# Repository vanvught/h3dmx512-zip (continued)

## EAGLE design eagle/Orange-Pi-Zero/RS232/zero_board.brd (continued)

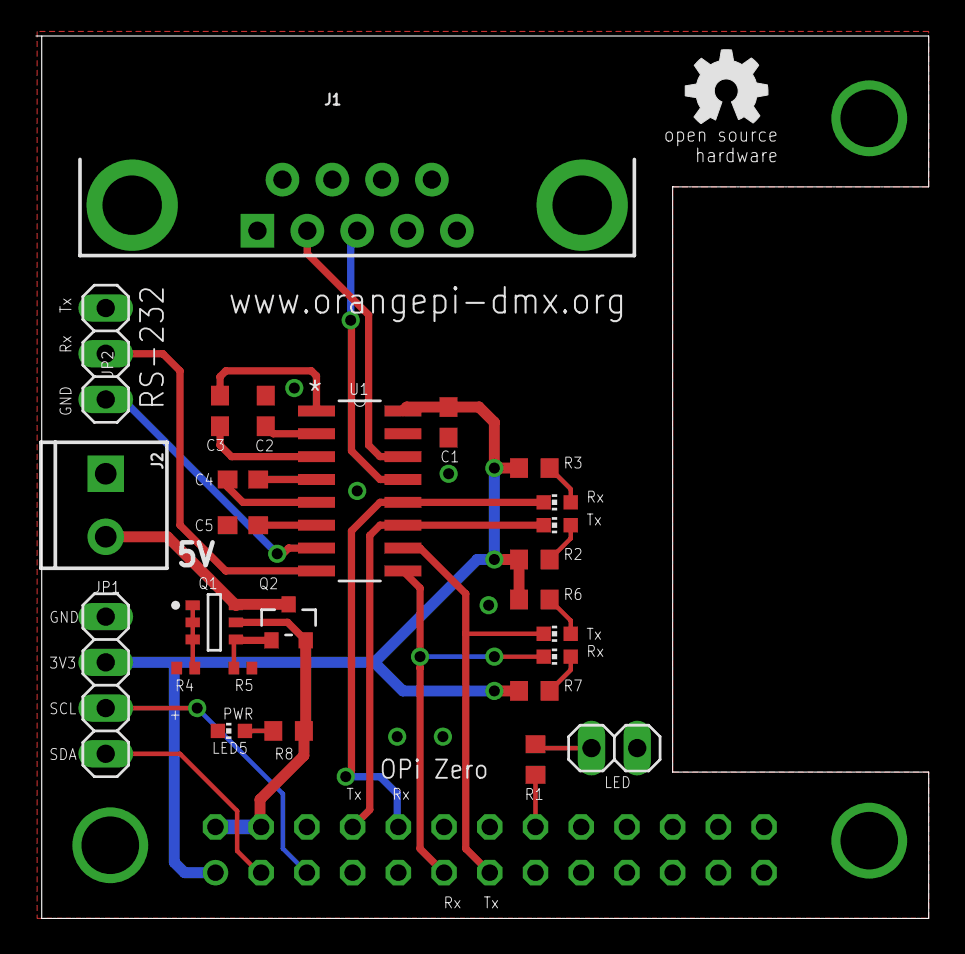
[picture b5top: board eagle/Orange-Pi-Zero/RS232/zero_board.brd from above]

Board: 2 copper layers, 49.6 x 49.0 mm, 28 parts (1 on the bottom side), 29 nets.

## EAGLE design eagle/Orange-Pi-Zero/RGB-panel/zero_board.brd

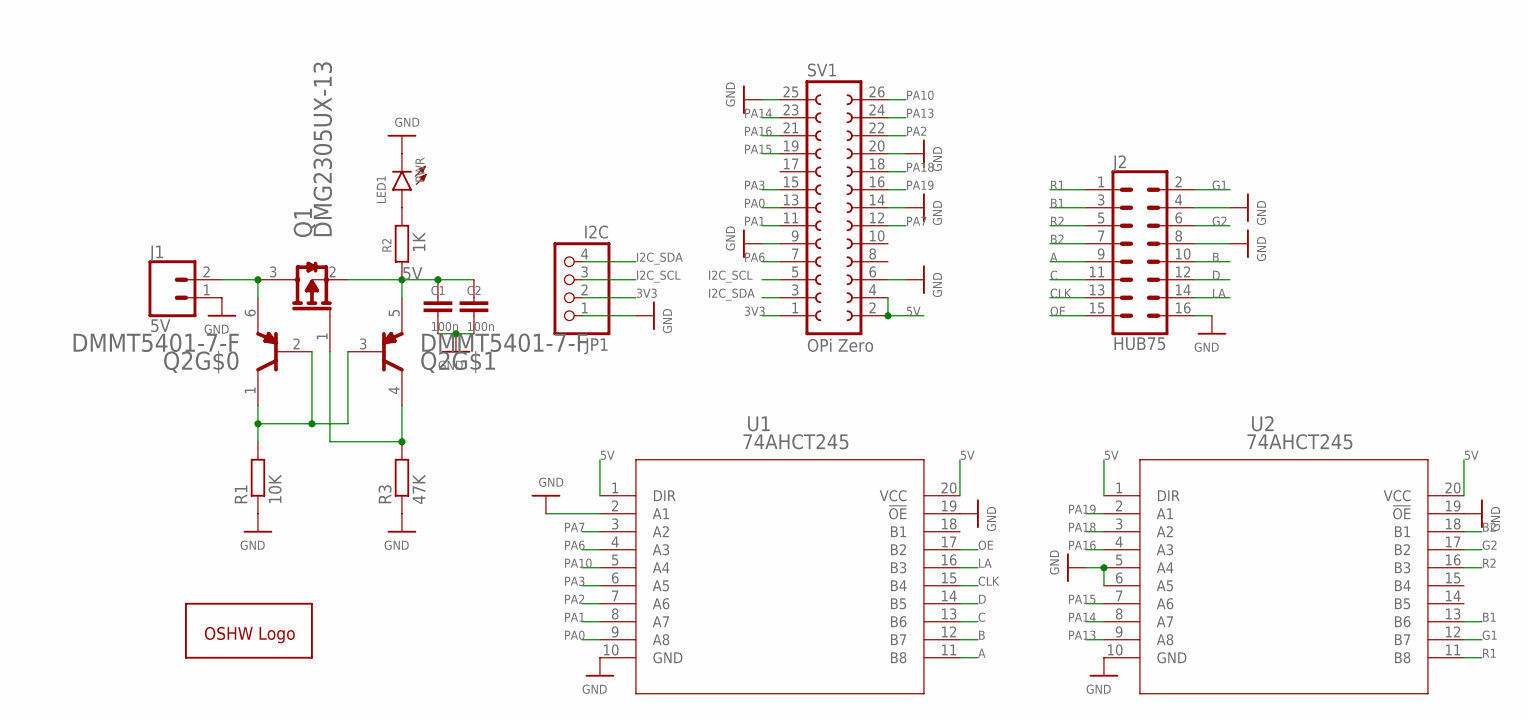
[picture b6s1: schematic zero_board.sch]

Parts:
C1, C2: 100n; C0603
GOLD_ORB_SM1: OSHWLOGOLOGO5MM; OSHW_5MM
J1: 5V; SCREWTERMINAL-3.5MM-2
J2: HUB75; 2X8-SHROUDED_LOCK
JP1: I2C; 1X04
LED1: PWR; CHIP-LED0603
Q1: DIODES_INC._DMG2305UX-13DIODES_INC._DMG2305UX-13_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; DIODES_INC._DMG2305UX-13_0
Q2: DIODES_DMMT5401-7-FDIODES_DMMT5401-7-F_0_0; DIODES_DMMT5401-7-F_0
R1: 10K; R0402
R2: 1K; R0603
R3: 47K; R0402
SV1: OPi Zero; FE13-2
U1, U2: 74AHCT245; PW20

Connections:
3V3: JP1.2, SV1.1
5V: C1.1, C2.1, Q1.2 (S), Q2.5 (E2), R2.1, SV1.2, SV1.4, U1.1 (DIR), U1.20 (VCC), U2.1 (DIR), U2.20 (VCC)
A: J2.9, U1.11 (B8)
B: J2.10, U1.12 (B7)
B1: J2.3, U2.13 (B6)
B2: J2.7, U2.18 (B1)
C: J2.11, U1.13 (B6)
CLK: J2.13, U1.15 (B4)
D: J2.12, U1.14 (B5)
G1: J2.2, U2.12 (B7)
G2: J2.6, U2.17 (B2)
GND: C1.2, C2.2, J1.1, J2.4, J2.8, J2.16, JP1.1, LED1.C, R1.1, R3.1, SV1.6, SV1.9, SV1.14, SV1.20, SV1.25, U1.2 (A1), U1.10 (GND), U1.19 (!OE), U2.5 (A4), U2.6 (A5), U2.10 (GND), U2.19 (!OE)
I2C_SCL: JP1.3, SV1.5
I2C_SDA: JP1.4, SV1.3
LA: J2.14, U1.16 (B3)
unnamed: Q2.1 (C1), Q2.2 (B1), Q2.3 (B2), R1.2
unnamed: J1.2, Q1.3 (D), Q2.6 (E1)
unnamed: Q1.1 (G), Q2.4 (C2), R3.2
unnamed: LED1.A, R2.2
OE: J2.15, U1.17 (B2)
PA0: SV1.13, U1.9 (A8)
PA1: SV1.11, U1.8 (A7)
PA2: SV1.22, U1.7 (A6)
PA3: SV1.15, U1.6 (A5)
PA6: SV1.7, U1.4 (A3)
PA7: SV1.12, U1.3 (A2)
PA10: SV1.26, U1.5 (A4)
PA13: SV1.24, U2.9 (A8)
PA14: SV1.23, U2.8 (A7)
PA15: SV1.19, U2.7 (A6)
PA16: SV1.21, U2.4 (A3)
PA18: SV1.18, U2.3 (A2)
PA19: SV1.16, U2.2 (A1)
R1: J2.1, U2.11 (B8)
R2: J2.5, U2.16 (B3)

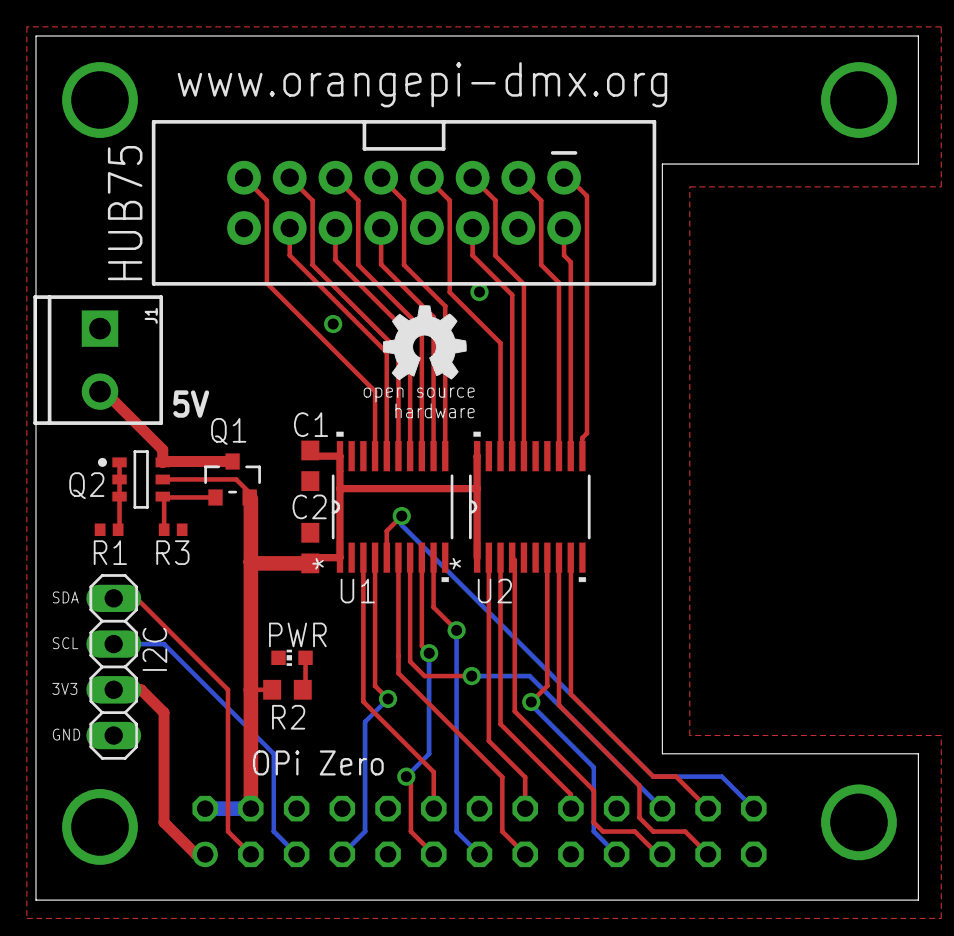
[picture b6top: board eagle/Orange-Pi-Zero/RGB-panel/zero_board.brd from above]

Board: 2 copper layers, 49.0 x 48.0 mm, 15 parts (1 on the bottom side), 35 nets.

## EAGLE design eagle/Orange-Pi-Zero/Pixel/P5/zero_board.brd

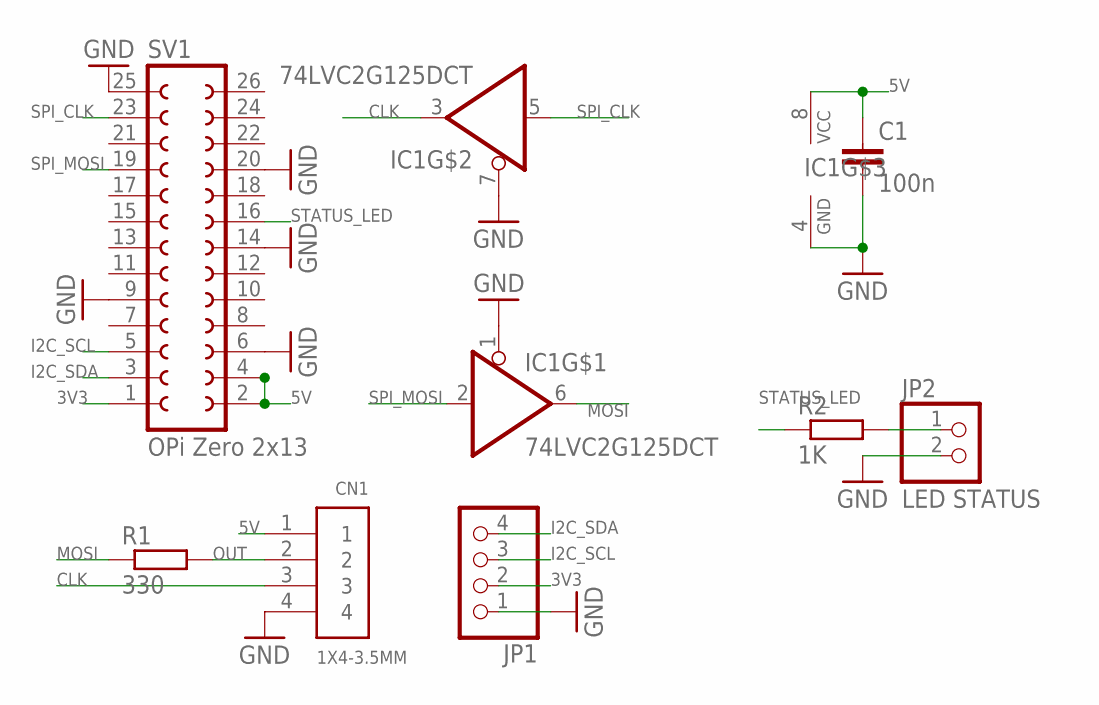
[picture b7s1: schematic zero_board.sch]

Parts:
C1: 100n; C0805
CN1: 1X4-3.5MM; 1X04-3.5MM
IC1: 74LVC2G125DCT; SSOP08
JP1: PINHD-1X4; 1X04
JP2: LED STATUS; 1X02
R1: 330; R0805
R2: 1K; R0805
SV1: OPi Zero 2x13; FE13-2

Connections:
3V3: JP1.2, SV1.1
5V: C1.1, CN1.1, IC1.8 (VCC), SV1.2, SV1.4
CLK: CN1.3, IC1.3 (O)
GND: C1.2, CN1.4, IC1.1 (OE), IC1.4 (GND), IC1.7 (OE), JP1.1, JP2.2, SV1.6, SV1.9, SV1.14, SV1.20, SV1.25
I2C_SCL: JP1.3, SV1.5
I2C_SDA: JP1.4, SV1.3
MOSI: IC1.6 (O), R1.1
unnamed: JP2.1, R2.2
OUT: CN1.2, R1.2
SPI_CLK: IC1.5 (I), SV1.23
SPI_MOSI: IC1.2 (I), SV1.19
STATUS_LED: R2.1, SV1.16

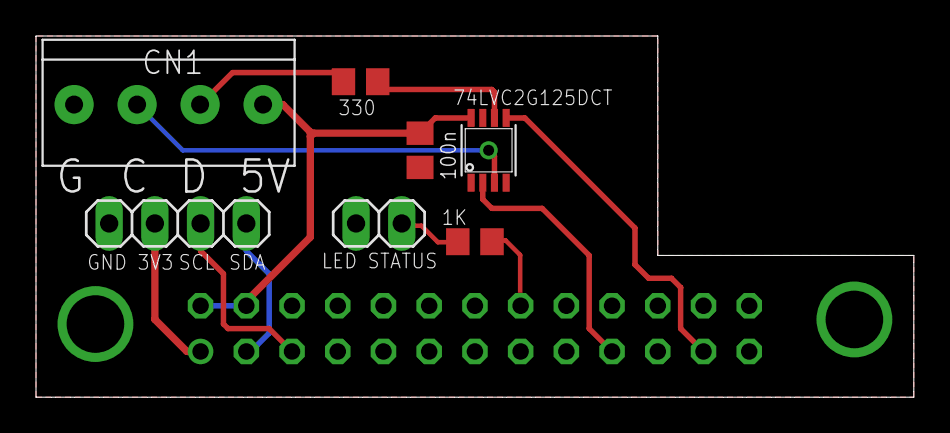
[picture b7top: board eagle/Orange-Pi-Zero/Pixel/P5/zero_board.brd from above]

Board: 2 copper layers, 48.8 x 20.1 mm, 8 parts (1 on the bottom side), 12 nets.

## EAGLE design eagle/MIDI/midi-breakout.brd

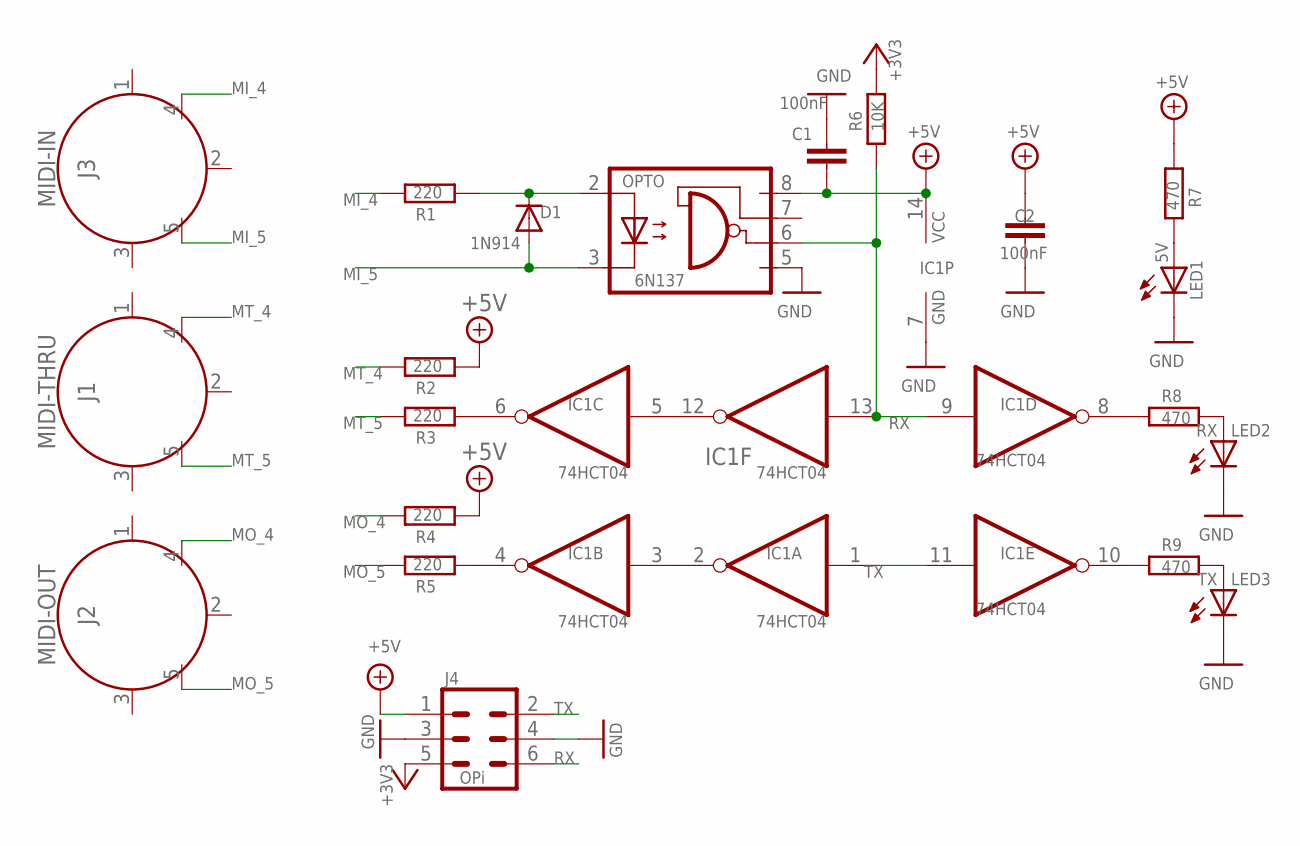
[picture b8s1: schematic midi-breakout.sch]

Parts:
C1, C2: 100nF; C050-024X044
D1: 1N914; D-5
IC1: 74HCT04; DIL14
J1: MIDI-THRU; DIN5-RA-PTH
J2: MIDI-OUT; DIN5-RA-PTH
J3: MIDI-IN; DIN5-RA-PTH
J4: OPi; 2X3-SHROUDED
LED1: 5V; LED3MM
LED2: RX; LED3MM
LED3: TX; LED3MM
OPTO: 6N137; DIL08
R1, R2, R3, R4, R5: 220; 0204/5
R6: 10K; 0204/5
R7, R8, R9: 470; 0204/5

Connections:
+3V3: J4.5, R6.2
+5V: C1.2, C2.2, IC1.14 (VCC), J4.1, OPTO.8 (VCC), R2.1, R4.1, R7.1
GND: C1.1, C2.1, IC1.7 (GND), J4.3, J4.4, LED1.K (C), LED2.K (C), LED3.K (C), OPTO.5 (GND)
MI_4: J3.4, R1.2
MI_5: D1.A, J3.5, OPTO.3 (C)
MO_4: J2.4, R4.2
MO_5: J2.5, R5.2
MT_4: J1.4, R2.2
MT_5: J1.5, R3.2
unnamed: IC1.8 (O), R8.1
unnamed: IC1.10 (O), R9.1
unnamed: LED3.A, R9.2
unnamed: LED2.A, R8.2
unnamed: IC1.5 (I), IC1.12 (O)
unnamed: D1.C, OPTO.2 (A), R1.1
unnamed: LED1.A, R7.2
unnamed: IC1.6 (O), R3.1
unnamed: IC1.2 (O), IC1.3 (I)
unnamed: IC1.4 (O), R5.1
RX: IC1.9 (I), IC1.13 (I), J4.6, OPTO.6 (VO), R6.1
TX: IC1.1 (I), IC1.11 (I), J4.2

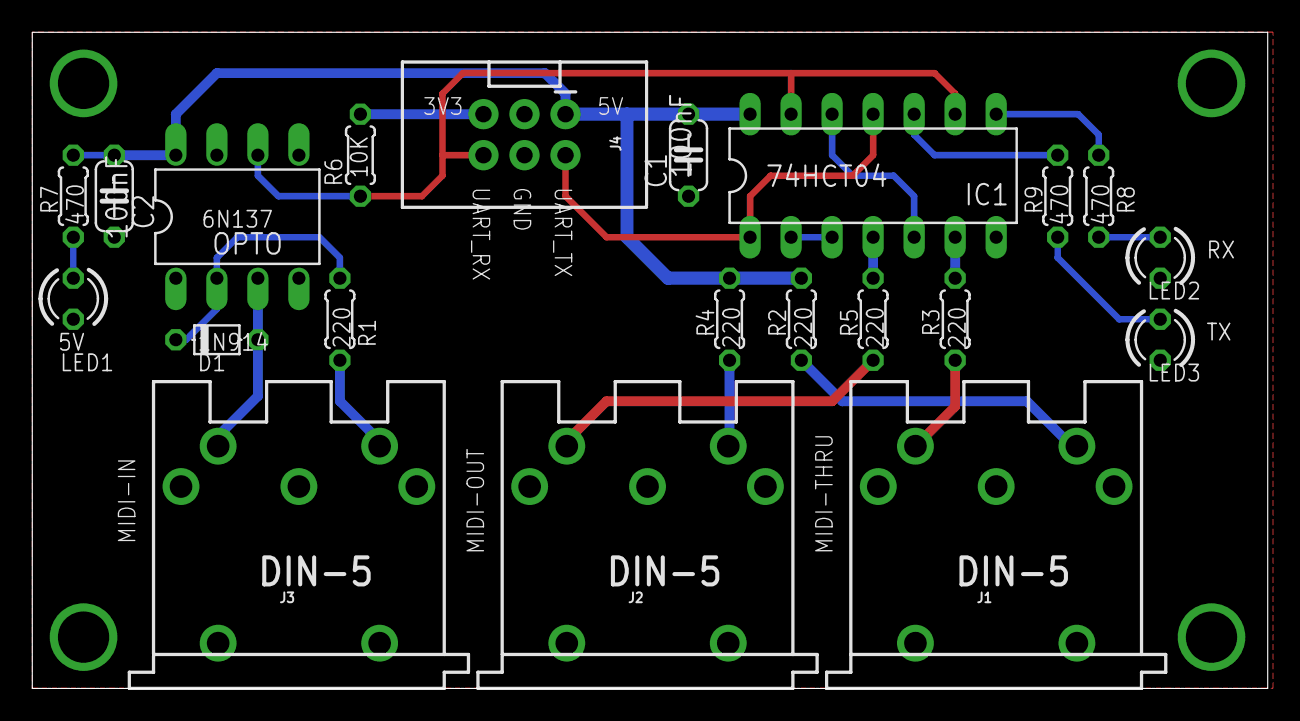
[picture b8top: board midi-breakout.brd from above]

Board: 2 copper layers, 76.5 x 40.6 mm, 21 parts (0 on the bottom side), 21 nets.

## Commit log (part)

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2024-10-01 V4.5
2024-10-01 V3.1
2024-10-01 V2.8
2024-10-01 V2.4
2024-10-01 V3.0
2024-10-01 V3.3
2024-10-01 V3.5
2024-10-01 V3.2
2024-10-01 V4.6
2024-10-01 V4.2
2024-10-01 V4.9
2024-10-01 V5.0
2024-11-17 V2.5
2024-11-17 V1.6
2024-11-17 V1.7
2024-11-17 V2.1
2024-11-17 V2.9
2024-11-17 V3.7
2024-11-17 V4.3
2024-11-17 V4.7
2024-11-17 V3.6
2024-11-17 V3.9
2024-11-17 V3.4
2024-11-17 V5.1
2024-12-27 V1.8
2024-12-27 V2.6
2024-12-27 V2.2
2024-12-27 V4.8
2024-12-27 V3.8
2024-12-27 V4.4
2024-12-27 V4.0
2024-12-27 V5.2
2025-02-07 V2.3
2025-02-07 V2.7
2025-02-07 V1.9
2025-02-07 V4.1
2025-02-07 V5.3
2026-02-23 V2.0
2026-02-23 V6.0
2026-02-23 Mark Remote Config UI as legacy; delete zip
    Update README: change 'Remote Configuration Manager' header to 'Remote Configuration Manager [Legacy]'. Remove opi_emac_eve_example.zip binary from the repository.
2026-03-13 V1.1
2026-03-13 V6.1
2026-03-19 V6.2
2026-03-19 V1.2
2026-03-29 V6.3
2026-03-29 V1.3
